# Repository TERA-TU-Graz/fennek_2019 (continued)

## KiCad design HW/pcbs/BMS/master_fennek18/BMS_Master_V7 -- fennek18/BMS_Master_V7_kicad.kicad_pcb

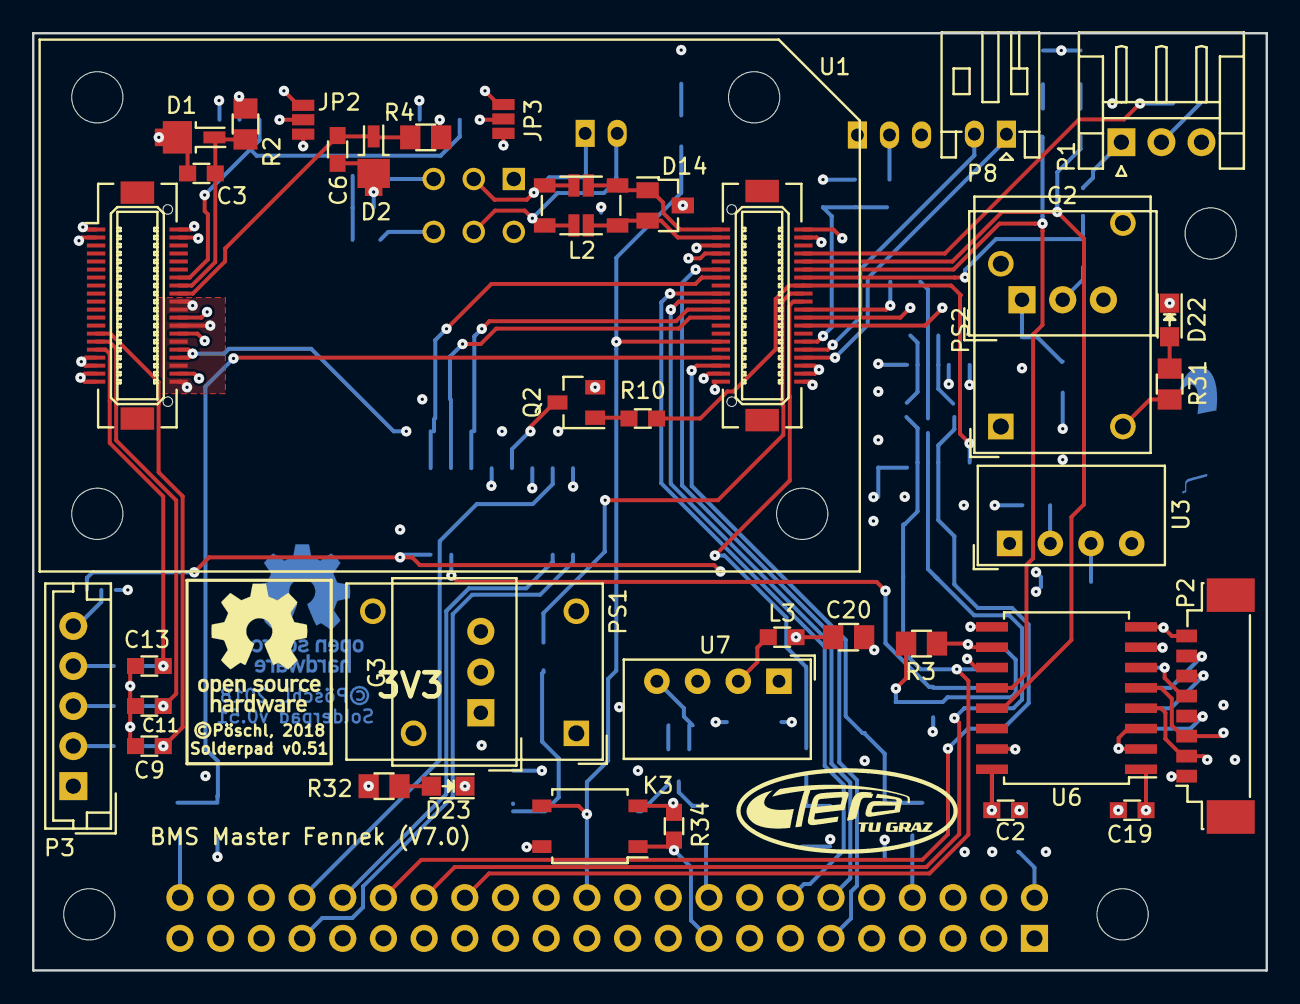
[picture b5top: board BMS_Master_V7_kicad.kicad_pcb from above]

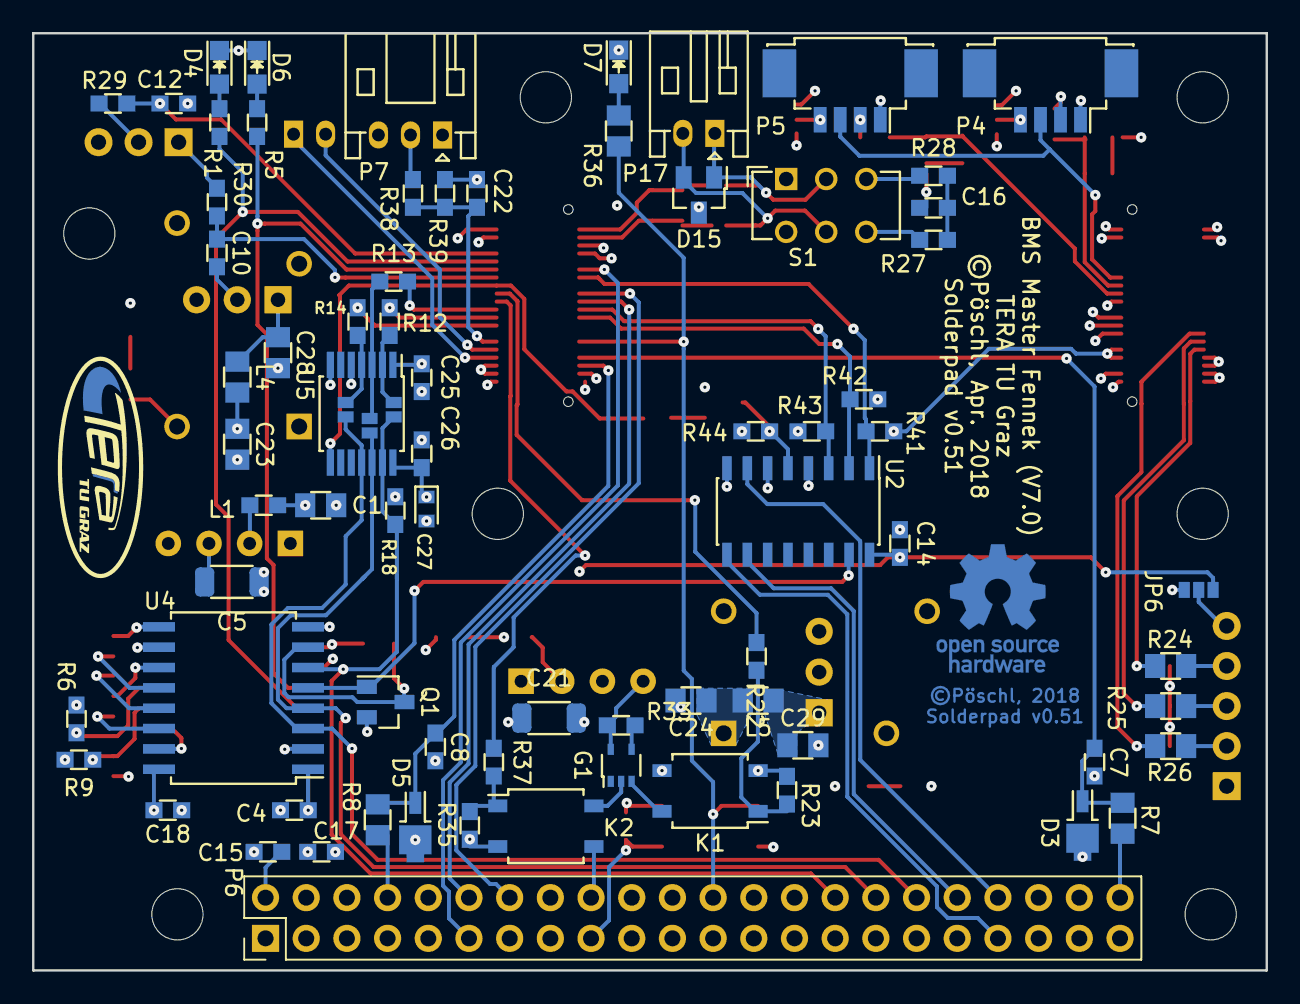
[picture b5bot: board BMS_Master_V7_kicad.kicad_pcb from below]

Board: 4 copper layers, 77.0 x 58.5 mm, 118 parts (77 on the bottom side), 92 nets.

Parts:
C1, C20: 4.7uF 25V; C_0805in
C2, C3, C4, C6, C7, C8, C9, C10, C11, C12, C13, C14, C15, C17, C18, C19, C22, C25, C26: 100n; C_0603in
C5, C21: 220pF 2kV; C_1206in_HV
C16: 47nF; C_0603in
C23, C24, C28, C29: 4u7; C_0805in
C27: 1u; TantalC_SizeM-1608mm_H0.9mm
D1, D2, D3, D5: 3V3; DO-216AA
D4: ~Alert; LED_0805
D6: ~Fault; LED_0805
D7: IL_OK; LED_0805
D14, D15: SUPPRESSOR; SOT-23
D22: 5V_OK; LED_0805
D23: 3V3_OK; LED_0805
G1: PSSI2021SAY
G2: TSR_0.5-2450; TSR_0.5
G3: TSR_0.5-2433; TSR_0.5
JP1, JP4, JP5: Jumper_NO_Small; SOLDERJUMPER_2_1mm
JP2, JP3: JUMPER3_NO; SOLDERJUMPER_3
JP6: JUMPER3_NO; SOLDERJUMPER_3_1mm
JP9, JP10: Jumper_NO_Small; SOLDERJUMPER_2
K1, K2, K3: ASSR-1218; SO-4
L1, L3: 4.7uH 50mA; L_0603in
L2: CM_CHOKE; L_ACT45B-XXX-2P_common-mode-choke
L4, L5: 3u3; L_0805in
P1: Buttons; JST_EH_S03B-EH_03x2.50mm_Angled
P2: Host_slave; Molex_PicoBlade_53398-0871_08x1.25mm_Straight
P3: ExtGPIO; JST_EH_B05B-EH-A_05x2.50mm_Straight
P4, P5: LEM; Molex_PicoBlade_53261-0471_04x1.25mm_Angled
P6: CONN_02X22; DW-22-08-L-D-200
P7: WheelSpeed; JST_PH_S3B-PH-K_03x2.00mm_Angled
P8, P17: CAN_CON_2pol; JST_PH_S2B-PH-K_02x2.00mm_Angled
PS1: Stepdown_v6-3V3; DCDC_Stepdown_v6
PS2: Stepdown_v6-5V; DCDC_Stepdown_v6
Q1, Q2: BSS205N
R1, R5: 5k1; R_0603in
R2, R4, R7, R8, R24, R25, R26: 1K; R_0805in
R3: 10k; R_0805in
R6, R9, R18: 100k; R_0603in
R10: 1k; R_0603in
R12, R13, R14: 100R; R_0603in
R22, R37: 470; R_0603in
R23, R29, R30, R34, R35: 1K; R_0603in
R27, R28: 60R; R_0603in
R31, R36: 5k1; R_0805in
R32: 2k2; R_0805in
R33: 120R; R_0603in
R38: 0R; R_0603in
R39: 22k; R_0603in
R41, R42, R43, R44: 10k; R_0603in
S1: SWITCH_DPDT; CuK_JS202011CQN_DPDT
U1: STM32f4_board_v3-1; STM32f4-board_v3-1
U2: SN74HC138DR
U3: Muarta_LME1205SC; Muarta_LME-SIP
U4, U6: ISO7241
U5: MAX3390EEUD
U7: Muarta_LME1212SC; Muarta_LME-SIP
svg2mod: G***; TERA_Logo_SilkS_5x12.5mm
svg2mod#2: G***; TERA_Logo_SilkS_and_Cu_5x12.5mm

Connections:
+3V3: C25.2, G3.3, JP2.3, JP3.3, JP6.1, P6.6, P6.42, PS1.2, R32.1, U1.2, U1.17, U1.18, U1.22, U1.27, U1.29, U1.39, U1.44, U1.59, U1.62, U1.63, U1.79, U5.1
+5V: C2.1, C4.1, C14.2, C26.1, C27.1, G2.3, JP2.1, JP3.1, JP6.3, K3.4, P1.3, P6.28, P7.3, PS2.2, R3.1, R31.1, R41.1, R42.1, R43.1, R44.2, U1.24, U1.25, U2.6, U2.16, U4.1, U5.14, U6.10, U6.16
+5V_SLAVE: C18.2, C19.2, P2.1, U3.4, U4.10, U4.16, U6.1, U6.7
+12V: C1.1, C17.2, C20.1, C23.1, C24.1, L1.2, L3.2, L4.2, L5.2, P6.4, PS1.1, PS2.1
/12V_Relay_Fault: P6.11, U1.46
/Alegro_1: P6.44, R7.1
/Alegro_1_Filtered: C7.1, D3.1, R7.2, U1.57
/Alegro_2: P6.8, R8.1
/Alegro_2_Filtered: C8.1, D5.1, R8.2, U1.58
/Button_Off: C10.1, R30.2, U1.74
/Button_On: C12.1, R29.2, U1.77
/CAN/CAN1+: P8.2, U1.65
/CAN/CAN1-: P8.1, U1.64
/CAN/CAN2+: D14.2, JP10.1, L2.2, U1.42
/CAN/CAN2-: D14.1, JP9.1, L2.3, U1.41
/CAN/CANperi+: D15.2, JP10.2, L2.1, P17.2, S1.5
/CAN/CANperi-: D15.1, JP9.2, L2.4, P17.1, S1.2
/CS_B0: R41.2, U1.47, U2.1
/CS_B1: R42.2, U1.52, U2.2
/CS_B2: R43.2, U1.51, U2.3
/EXT_GPIO_1: C13.1, R24.2, U1.16
/EXT_GPIO_2: C11.1, R25.2, U1.15
/EXT_GPIO_3: C9.1, R26.2, U1.14
/IL_next+: K2.3, P6.18
/IL_next-: K3.1, P6.17, R34.1
/Interlock/IL_Iconst: G1.2, K2.4
/Interlock_OK: K3.3, P6.24, R36.2, U1.55
/Interlock_On1: R22.2, U1.72
/Interlock_On2: R37.1, U1.71
/LEM1: C3.1, D1.1, R2.2, U1.33
/LEM2: C6.1, D2.1, R4.2, U1.32
/LEM_Standby: P4.3, P5.3, U1.34
/MISO: R12.2, U1.69
/MOSI: R13.2, U1.70
/Main Connector/+12VDC_BMS_Switched: C15.2, P6.2
/Main_Fault: P6.12, U1.50
/NALERT: R1.1, U1.76, U6.13
/NCS_12V_Relay: P6.37, U2.9
/NCS_MainRelay: P6.36, U2.10
/NCS_PreCharge: P6.38, U2.7
/NFAULT: R5.1, U1.75, U6.12
/Precharge_Fault: P6.14, U1.49
/SCLK: R14.2, U1.68
/SPI_CLK_5V: JP5.2, P6.34, U4.3, U5.11
/SPI_CS: R10.2, U1.73, U5.8
/SPI_Controller/MISO_1: JP1.1, R12.1, U5.2
/SPI_Controller/MOSI_1: JP4.1, R13.1, U5.3
/SPI_Controller/NCS1: Q1.1, U2.15, U4.5
/SPI_Controller/SCLK_1: JP5.1, R14.1, U5.4
/SPI_Controller/SPI Isolator/MISO_slave: P2.5, U4.11
/SPI_Controller/SPI Isolator/MOSI_Slave: P2.6, U4.13
/SPI_Controller/SPI Isolator/NCS_Slave: P2.7, U4.12
/SPI_Controller/SPI Isolator/SCLK_slave: P2.4, U4.14
/SPI_Controller/SPI Isolator/~Alert_slave: P2.2, R9.1, U6.4
/SPI_Controller/SPI Isolator/~Fault_slave: P2.3, R6.1, U6.5
/SPI_Controller/SPI_NCS_5V: Q2.3, R44.1, U2.5
/SPI_MISO_5V: JP1.2, P6.30, R18.1, U4.6, U5.13
/SPI_MOSI_5V: JP4.2, P6.32, U4.4, U5.12
/WheelSpeed: C22.1, R38.2, R39.2, U1.66
GND: C1.2, C2.2, C3.2, C4.2, C5.1, C6.2, C7.2, C8.2, C9.2, C10.2, C11.2, C12.2, C13.2, C14.1, C15.1, C16.2, C17.1, C20.2, C21.1, C22.2, C23.2, C24.2, C25.1, C26.2, C27.2, C28.2, C29.2, D1.2, D2.2, D3.2, D4.1, D5.2, D6.1, D7.1, D14.3, D15.3, D22.1, D23.1, G2.2, G3.2, K1.2, K2.2, P3.1, P4.1, P5.1, P6.1, P6.3, P6.5, P6.7, P6.9, P6.10, P6.13, P6.21, P6.22, P6.23, P6.25, P6.26, P6.27, P6.29, P6.31, P6.33, P6.35, P6.39, P6.40, P6.41, P6.43, P7.1, PS1.3, PS1.4, PS2.3, PS2.4, Q1.2, Q2.2, R18.2, R23.2, R35.2, R39.1, U1.1, U1.19, U1.20, U1.21, U1.23, U1.26, U1.28, U1.30, U1.31, U1.40, U1.43, U1.60, U1.61, U1.80, U2.4, U2.8, U3.1, U4.2, U4.8, U5.5, U5.7, U6.9, U6.11, U6.15, U7.1
GND_slave: C5.2, C18.1, C19.1, P2.8, R6.2, R9.2, U3.3, U4.9, U4.15, U6.2, U6.3, U6.8
IL_V+: G1.5, R33.1, U7.4
IL_V-: C21.2, K1.3, K3.2, R34.2, U7.3
unnamed: C16.1, R27.2, R28.2
unnamed: C28.1, G2.1, L4.1
unnamed: C29.1, G3.1, L5.1
unnamed: D4.2, R1.2
unnamed: D6.2, R5.2
unnamed: D7.2, R36.1
unnamed: D22.2, R31.2
unnamed: D23.2, R32.2
unnamed: G1.3, K1.4
unnamed: G1.4, R33.2
unnamed: JP2.2, P4.4
unnamed: JP3.2, P5.4
unnamed: JP6.2, P3.5
unnamed: K1.1, R22.1, R23.1
unnamed: K2.1, R35.1, R37.2
unnamed: L1.1, U3.2
unnamed: L3.1, U7.2
unnamed: P1.1, R30.1
unnamed: P1.2, R29.1
unnamed: P3.2, R26.1
unnamed: P3.3, R25.1
unnamed: P3.4, R24.1
unnamed: P4.2, R2.1
unnamed: P5.2, R4.1
unnamed: P7.2, R38.1
unnamed: Q1.3, R3.2, U4.7
unnamed: Q2.1, R10.1
unnamed: R27.1, S1.6
unnamed: R28.1, S1.3

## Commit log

2020-02-26 Add KiCad projects from development repo
2020-02-26 add ecad libs as submodule
2020-02-26 add screenshot
